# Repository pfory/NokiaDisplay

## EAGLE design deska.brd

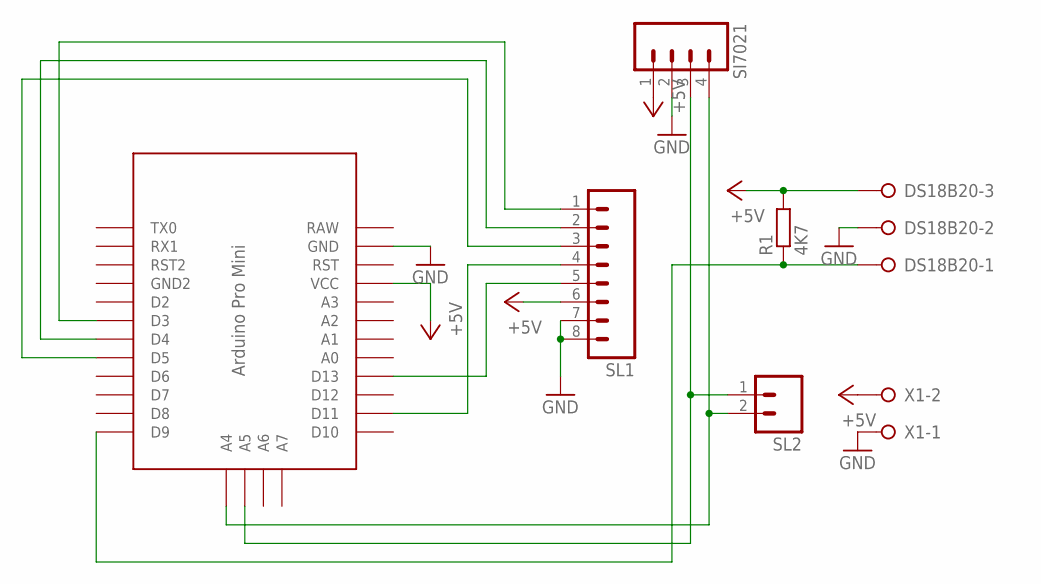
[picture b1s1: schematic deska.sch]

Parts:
DS18B20: W237-03P; W237-133
R1: 4K7; 0207/10
SI7021: M04; 04P
SL1: M08; 08P
SL2: M02; 02P
U$1: PRO-MINI
X1: W237-02P; W237-132

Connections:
+5V: DS18B20.3, R1.2, SI7021.1, SL1.6, U$1.VCC, X1.2
CE: SL1.2, U$1.D4
CLK: SL1.5, U$1.D13
DC: SL1.3, U$1.D5
DIN: SL1.4, U$1.D11
GND: DS18B20.2, SI7021.2, SL1.7, SL1.8, U$1.GND, X1.1
unnamed: DS18B20.1, R1.1, U$1.D9
RAW: U$1.RAW
RESET: SL1.1, U$1.D3
SCL: SI7021.3, SL2.1, U$1.A5
SDA: SI7021.4, SL2.2, U$1.A4

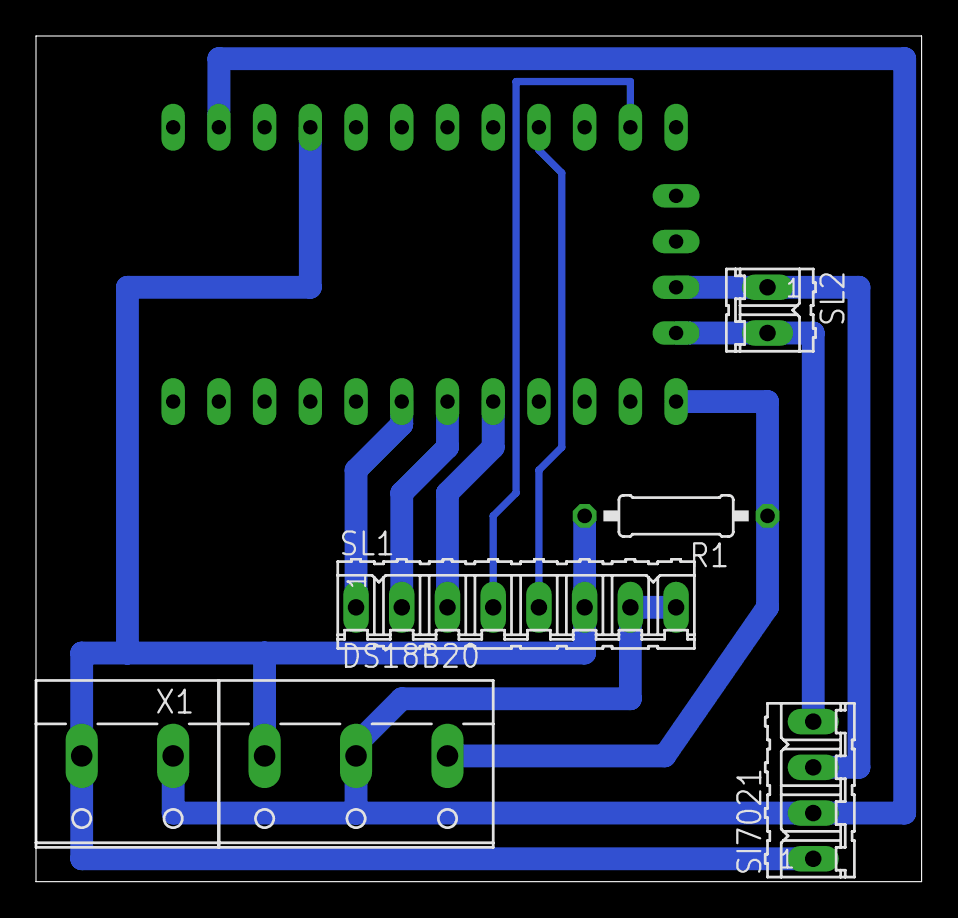
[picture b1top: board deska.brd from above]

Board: 2 copper layers, 49.2 x 47.0 mm, 7 parts (0 on the bottom side), 10 nets.

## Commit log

2016-06-28 initial
2016-10-19 nasazeno 19.10.2016
2016-10-24 +schema
2016-11-22 uprava desky
2017-01-10 +deska +ino
2019-03-04 nezobrazeni teploty pri chybe cidla
2020-03-23 v0.2 pokud selze teplotni sensor, zobrazi se posledni namerena hodnota
